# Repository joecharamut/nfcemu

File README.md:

# nfcemu

temporary name for a nfc tag emulation project

ideal goal is emulating an ntag215 (nfcA, type 2) compatible tag

code is targeting the ATTiny804 at the mo

inspired by https://github.com/Nonannet/simple-nfc

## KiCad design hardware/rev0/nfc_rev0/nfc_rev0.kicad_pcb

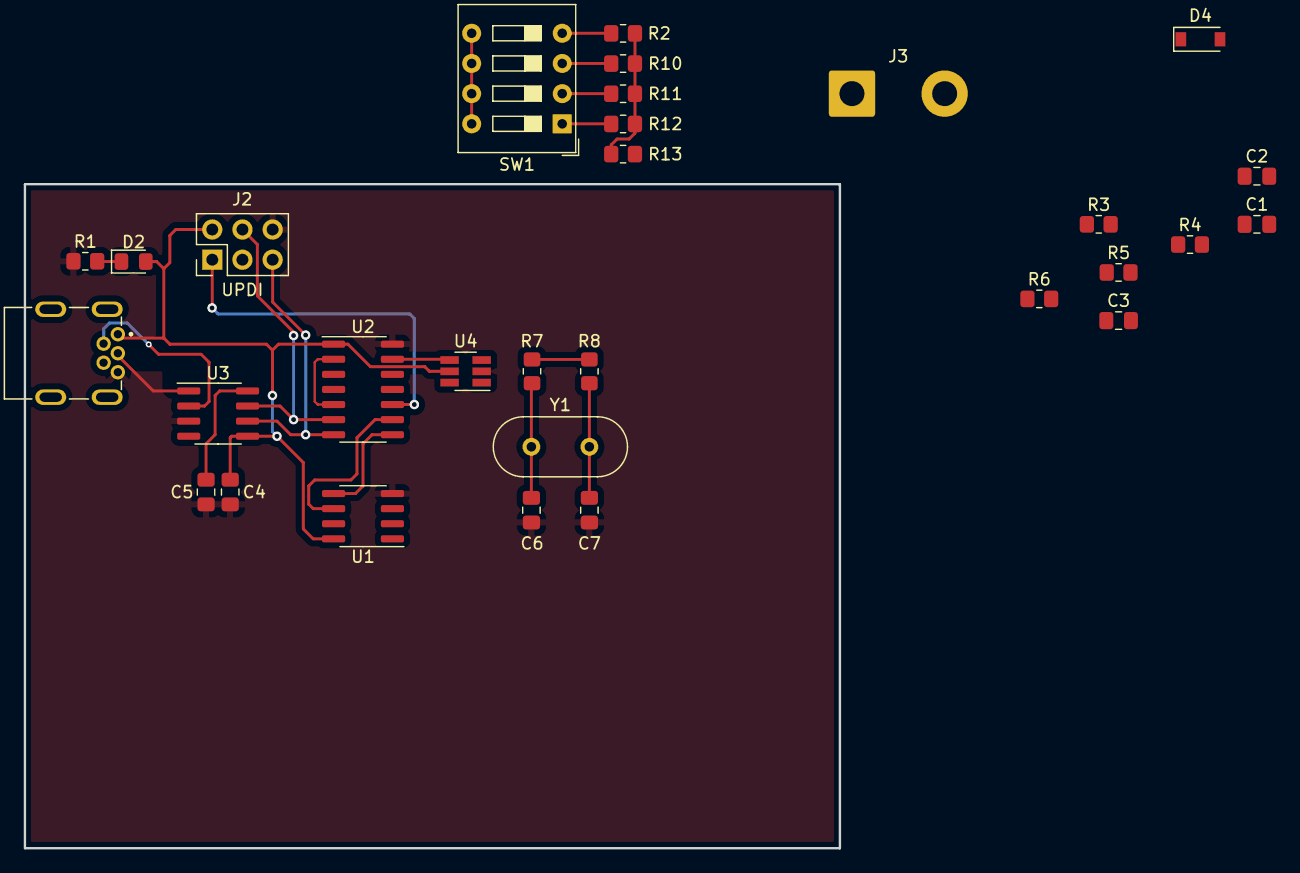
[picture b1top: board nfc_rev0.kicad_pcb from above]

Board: 2 copper layers, 68.6 x 55.9 mm, 30 parts (0 on the bottom side), 24 nets.

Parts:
C1: 100pF; C_0805_2012Metric_Pad1.18x1.45mm_HandSolder
C2: 180pF; C_0805_2012Metric_Pad1.18x1.45mm_HandSolder
C3: 10nF; C_0805_2012Metric_Pad1.18x1.45mm_HandSolder
C4, C5: 100nF; C_0805_2012Metric_Pad1.18x1.45mm_HandSolder
C6, C7: 20pF; C_0805_2012Metric_Pad1.18x1.45mm_HandSolder
D2: LED; LED_0805_2012Metric_Pad1.15x1.40mm_HandSolder
D4: D_Schottky; D_SOD-123
J1: USB_B_Mini; OMRON_XM7D-0512
J2: UPDI; PinHeader_2x03_P2.54mm_Vertical
J3: Conn_01x02; SolderWire-1.5sqmm_1x02_P7.8mm_D1.7mm_OD3.9mm
R1: 1k; R_0805_2012Metric_Pad1.20x1.40mm_HandSolder
R2: 80k; R_0805_2012Metric_Pad1.20x1.40mm_HandSolder
R3: 2k; R_0805_2012Metric_Pad1.20x1.40mm_HandSolder
R4, R5, R11: 20k; R_0805_2012Metric_Pad1.20x1.40mm_HandSolder
R6: 470; R_0805_2012Metric_Pad1.20x1.40mm_HandSolder
R7: 1M; R_0805_2012Metric_Pad1.20x1.40mm_HandSolder
R8: 270; R_0805_2012Metric_Pad1.20x1.40mm_HandSolder
R10: 40k; R_0805_2012Metric_Pad1.20x1.40mm_HandSolder
R12, R13: 10k; R_0805_2012Metric_Pad1.20x1.40mm_HandSolder
SW1: SW_DIP_x04; SW_DIP_SPSTx04_Slide_9.78x12.34mm_W7.62mm_P2.54mm
U1: MB85RC64TA; SOIC-8_3.9x4.9mm_P1.27mm
U2: ATtiny804-SS; SOIC-14_3.9x8.7mm_P1.27mm
U3: CH340N; SOIC-8_3.9x4.9mm_P1.27mm
U4: 74LVC2G14; SOT-23-6_Handsoldering
Y1: 13.56MHz; Crystal_HC49-U_Vertical

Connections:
/AIN1: R2.2, R10.2, R11.2, R12.2, R13.1, U2.11 (PA1)
/AINN0: C3.1, R4.2, R5.1, U2.4 (PA6)
/AINP0: R6.2, U2.2 (PA4), U2.5 (PA7)
/Antenna/ANT: C2.1, D4.1 (K), R3.1, R4.1, R6.1
/CLKI: U2.13 (PA3), U4.4
/RXD: J2.4, U2.6 (PB3), U3.7 (RXD)
/SCL: U1.6 (SCL), U2.9 (PB0)
/SDA: U1.5 (SDA), U2.8 (PB1)
/TXD: J2.5, U2.7 (PB2), U3.6 (TXD)
/UPDI: J2.1, U2.10 (~RESET/PA0)
GND: C1.2, C2.2, C3.2, C4.1, C5.2, C6.2, C7.2, J1.5 (GND), J2.6, J3.1, R1.2, R3.2, R5.2, R13.2, U1.4 (VSS), U2.14 (GND), U3.3 (GND), U4.2 (GND)
unnamed: C1.1, D4.2 (A), J3.2
unnamed: C5.1, U3.8 (V3)
unnamed: C6.1, R7.1, U4.1, Y1.1
unnamed: C7.1, R8.1, Y1.2
unnamed: D2.1 (K), R1.1
unnamed: J1.2 (D-), U3.2 (UD-)
unnamed: J1.3 (D+), U3.1 (UD+)
unnamed: R2.1, SW1.4
unnamed: R7.2, R8.2, U4.3, U4.6
unnamed: R10.1, SW1.3
unnamed: R11.1, SW1.2
unnamed: R12.1, SW1.1
VCC: C4.2, D2.2 (A), J1.1 (VBUS), J2.2, SW1.5, SW1.6, SW1.7, SW1.8, U1.8 (VDD), U2.1 (VCC), U3.5 (VCC), U4.5 (VCC)

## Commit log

2022-12-10 add license
2022-12-10 rename main
2022-12-10 add license header
2022-12-10 remove logging c binding
2022-12-10 remove old code
2022-12-10 copy paste ready code
2022-12-11 code
2022-12-11 impl sleep
2022-12-11 trying to get it working
2022-12-13 wip rewriting rx
2022-12-14 aaaaa
2022-12-17 still doesnt work
2022-12-23 before changing everything
2022-12-23 update platform & usart
2022-12-25 prob gonna rewrite the whole thing
2022-12-25 avr inits stuff to 0 by default
2022-12-27 basic building blocks rewritten for attiny804
2022-12-30 lots of stuff
2023-01-01 still trying to get stuff working
2023-01-01 dont really need that
2023-01-01 unused platformio defaults
2023-01-03 impl rx decoding in isr
2023-01-10 oof its starting to work again finally
2023-01-10 oh look at that it works at normal clock speed now
2023-01-10 cleanup some unused code
2023-01-10 testing
2023-01-10 separating out functions
2023-01-10 minor code cleanup
2023-01-10 comment
2023-01-10 move crc and add licence
2023-01-10 helper fns
2023-01-10 add doc comments for crc
2023-01-10 fix comment style
2023-01-11 reformat stuff
2023-01-11 split off common and t2t code
2023-01-11 move nfca code into a folder
2023-01-17 trying to get more tag stuff working
2023-01-17 protocol decoders for sigrok
2023-01-18 got the signal analysis working
2023-01-18 comment better
2023-01-18 fix comment
2023-01-18 add more comments to tag data
2023-01-18 move stuff into a sensible folder structure
2023-01-18 gross but ever so slightly closer to working
2023-01-18 use vport to save some clock cycles
2023-01-19 getting closer to working
2023-01-19 this is so annoying lol
2023-01-19 test
2023-01-21 aaaaaaaa
2023-01-26 still a wip
2023-01-26 add schematics
2023-01-26 work
2023-02-14 refactoring
2023-02-14 refactoring still woo
2023-02-19 still working on refactoring
2023-02-22 add some helpful stuff
2023-02-22 some change i guess
2023-02-22 code cleanup more more
2023-02-24 use lambda instead of macro for BIT()
2023-02-24 change setup to setStorage
2023-03-11 something
2023-03-19 trying to get debugging working still
